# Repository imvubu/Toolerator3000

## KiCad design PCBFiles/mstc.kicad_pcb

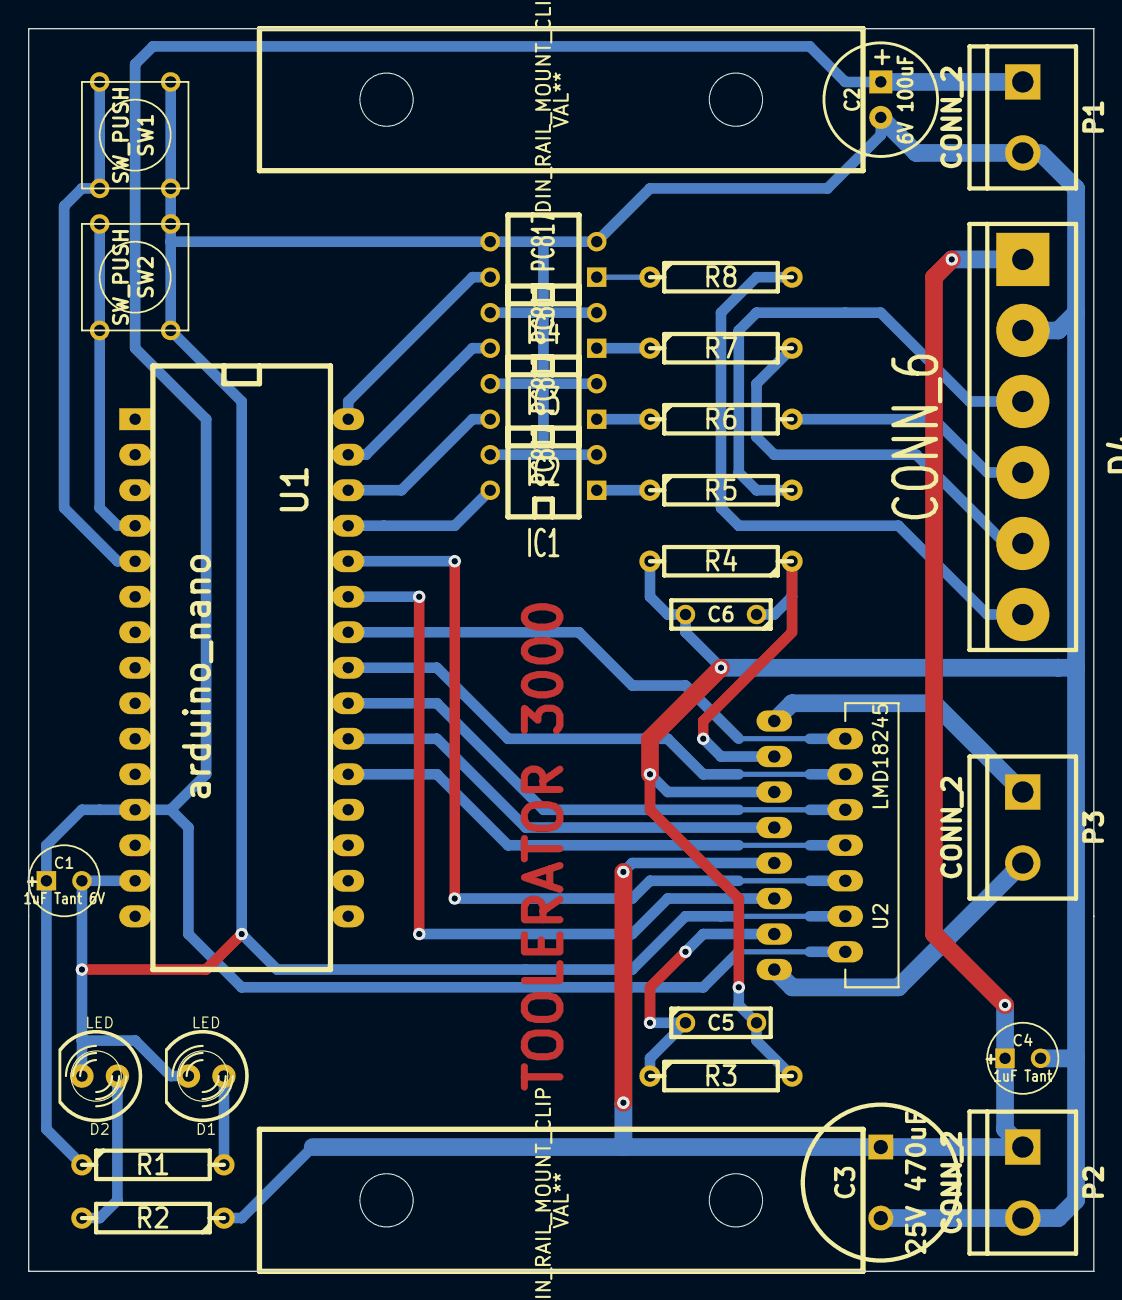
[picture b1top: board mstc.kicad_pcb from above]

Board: 2 copper layers, 76.2 x 88.9 mm, 30 parts (0 on the bottom side), 30 nets.

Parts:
C1: 1uF Tant 6V; C1V5
C2: 6V 100uF; C1V8
C3: 25V 470uF; C2V10
C4: 1uF Tant; C1V5
C5: 470pf; C2
C6: 0.002uF; C2
D1, D2: LED; LED-5MM
DIN_RAIL_MOUNT_CLIP: VAL**; DIN_RAIL_MOUNT_CLIP
DIN_RAIL_MOUNT_CLIP#2: VAL**; DIN_RAIL_MOUNT_CLIP
IC1, IC2, IC3, IC4: PC817; DIP-4__300
P1, P2, P3: CONN_2; bornier2
P4: CONN_6; bornier6
R1: 220; R4
R2: 2.2K; R4
R3: 6.25K; R4
R4: 20K; R4
R5, R6, R7, R8: 3.3K; R4
SW1, SW2: SW_PUSH; SW_PUSH_SMALL
U1: arduino_nano; arduino_mini
U2: LMD18245; TO-220-15

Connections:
+5V: C1.1, C2.1, P1.1, R1.1, U1.12, U2.14
+24V: C3.1, C4.1, P2.1, P4.1, R2.1, U2.9
GND: C1.2, C2.2, C3.2, C4.2, C5.2, C6.2, D1.2, D2.2, IC1.2, IC1.3, IC2.2, IC2.3, IC3.2, IC3.3, IC4.2, IC4.3, P1.2, P2.2, P4.2, R3.2, R4.2, SW1.1, SW2.1, U1.14, U2.5, U2.12
unnamed: C5.1, R3.1, U2.13
unnamed: C6.1, R4.1, U2.3
unnamed: D1.1, R1.2
unnamed: D2.1, R2.2
unnamed: IC1.1, R5.1
unnamed: IC1.4, U1.27
unnamed: IC2.1, R6.1
unnamed: IC2.4, U1.28
unnamed: IC3.1, R7.1
unnamed: IC3.4, U1.29
unnamed: IC4.1, R8.1
unnamed: IC4.4, U1.30
unnamed: P3.1, U2.1
unnamed: P3.2, U2.15
unnamed: P4.3, R5.2
unnamed: P4.4, R6.2
unnamed: P4.5, R7.2
unnamed: P4.6, R8.2
unnamed: SW1.2, U1.5
unnamed: SW2.2, U1.4
unnamed: U1.20, U2.8
unnamed: U1.21, U2.7
unnamed: U1.22, U2.6
unnamed: U1.23, U2.4
unnamed: U1.24, U2.2
unnamed: U1.25, U2.11
unnamed: U1.26, U2.10
